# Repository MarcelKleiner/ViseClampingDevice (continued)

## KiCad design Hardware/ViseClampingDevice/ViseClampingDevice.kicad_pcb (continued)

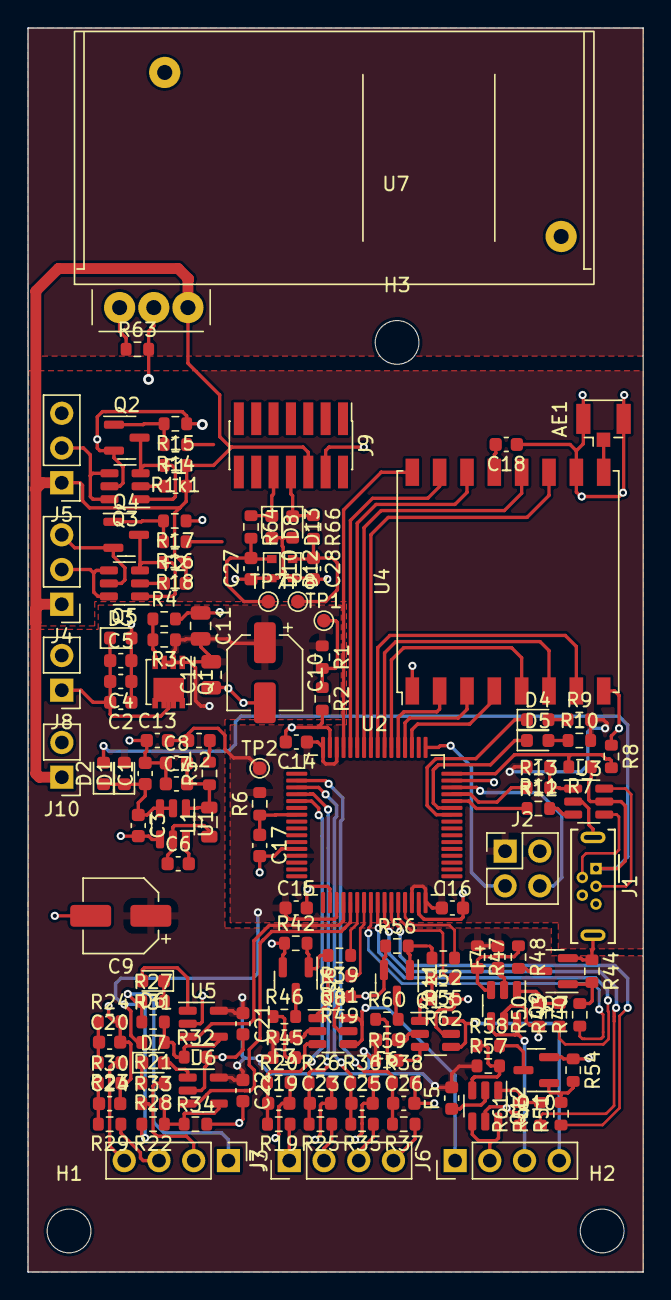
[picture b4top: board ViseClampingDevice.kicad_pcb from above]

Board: 2 copper layers, 45.0 x 91.0 mm, 151 parts (0 on the bottom side), 107 nets.

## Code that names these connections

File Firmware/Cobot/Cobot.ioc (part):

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Mcu.Name=STM32L433RCTxP
Mcu.Package=LQFP64
Mcu.UserName=STM32L433RCTxP
PA0.GPIOParameters=GPIO_Label
PA0.GPIO_Label=DI_6
PA0.Signal=GPIO_Input
PA1.GPIOParameters=GPIO_Label
PA1.GPIO_Label=DI_7
PA1.Signal=GPIO_Input
PA10.GPIOParameters=GPIO_Label
PA10.GPIO_Label=LED_G
PA10.Signal=GPIO_Output
PA11.Mode=Device
PA11.Signal=USB_DM
PA12.Mode=Device
PA12.Signal=USB_DP
PA13\ (JTMS-SWDIO).Mode=Serial_Wire
PA13\ (JTMS-SWDIO).Signal=SYS_JTMS-SWDIO
PA14\ (JTCK-SWCLK).Mode=Serial_Wire
PA14\ (JTCK-SWCLK).Signal=SYS_JTCK-SWCLK
PA2.GPIOParameters=GPIO_Label
PA2.GPIO_Label=DI_8
PA2.Signal=GPIO_Input
PA4.Signal=COMP_DAC11_group
PA5.Signal=COMP_DAC12_group
PA6.Signal=ADCx_IN11
PA7.Signal=ADCx_IN12
PA8.GPIOParameters=GPIO_Label
PA8.GPIO_Label=DI_OUT_1_P
PA8.Signal=GPIO_Output
PA9.GPIOParameters=GPIO_Label
PA9.GPIO_Label=LED_R
PA9.Signal=GPIO_Output
PB0.GPIOParameters=GPIO_Label
PB0.GPIO_Label=DI_OUT_4_P
PB0.Signal=GPIO_Output
PB1.GPIOParameters=GPIO_Label
PB1.GPIO_Label=DI_OUT_6_P
PB1.Signal=GPIO_Output
PB10.GPIOParameters=GPIO_Label
PB10.GPIO_Label=DI_OUT_4_N
PB10.Signal=GPIO_Output
PB11.GPIOParameters=GPIO_Label
PB11.GPIO_Label=DI_OUT_2_P
PB11.Signal=GPIO_Output
PB13.GPIOParameters=GPIO_Label
PB13.GPIO_Label=DI_OUT_7_N
PB13.Signal=GPIO_Output
PB14.GPIOParameters=GPIO_Label
PB14.GPIO_Label=DI_OUT_7_P
PB14.Signal=GPIO_Output
PB15.GPIOParameters=GPIO_Label
PB15.GPIO_Label=DI_OUT_5_N
PB15.Signal=GPIO_Output
PB2.GPIOParameters=GPIO_Label
PB2.GPIO_Label=DI_OUT_2_N
PB2.Signal=GPIO_Output
PB3\ (JTDO-TRACESWO).GPIOParameters=GPIO_Label
PB3\ (JTDO-TRACESWO).GPIO_Label=RFM_NSS
PB3\ (JTDO-TRACESWO).Signal=GPIO_Output
PB4\ (NJTRST).GPIOParameters=GPIO_Label
PB4\ (NJTRST).GPIO_Label=RFM_RST
PB4\ (NJTRST).Signal=GPIO_Output
PB5.GPIOParameters=GPIO_Label
PB5.GPIO_Label=RFM_DI_3
PB5.Signal=GPIO_Output
PB6.GPIOParameters=GPIO_Label
PB6.GPIO_Label=RFM_DI_0
PB6.Signal=GPIO_Output
PB7.GPIOParameters=GPIO_Label
PB7.GPIO_Label=RFM_DI_2
PB7.Signal=GPIO_Output
PC0.GPIOParameters=GPIO_Label
PC0.GPIO_Label=DI_2
PC0.Signal=GPIO_Input
PC1.GPIOParameters=GPIO_Label
PC1.GPIO_Label=DI_3
PC1.Signal=GPIO_Input
PC10.Mode=Full_Duplex_Master
PC10.Signal=SPI3_SCK
PC11.Mode=Full_Duplex_Master
PC11.Signal=SPI3_MISO
PC12.Mode=Full_Duplex_Master
PC12.Signal=SPI3_MOSI
PC14-OSC32_IN\ (PC14).GPIOParameters=GPIO_Label
PC14-OSC32_IN\ (PC14).GPIO_Label=DI_OUT_8_P
PC14-OSC32_IN\ (PC14).Signal=GPIO_Output
PC15-OSC32_OUT\ (PC15).GPIOParameters=GPIO_Label
PC15-OSC32_OUT\ (PC15).GPIO_Label=DI_OUT_8_N
PC15-OSC32_OUT\ (PC15).Signal=GPIO_Output
PC2.GPIOParameters=GPIO_Label
PC2.GPIO_Label=DI_4
PC2.Signal=GPIO_Input
PC3.GPIOParameters=GPIO_Label
PC3.GPIO_Label=DI_5
PC3.Signal=GPIO_Input
PC4.GPIOParameters=GPIO_Label
PC4.GPIO_Label=DI_OUT_6_N
PC4.Signal=GPIO_Output
PC6.GPIOParameters=GPIO_Label
PC6.GPIO_Label=DI_OUT_5_P
PC6.Signal=GPIO_Output
PC7.GPIOParameters=GPIO_Label
PC7.GPIO_Label=DI_OUT_3_N
PC7.Signal=GPIO_Output
PC8.GPIOParameters=GPIO_Label
PC8.GPIO_Label=DI_OUT_3_P
PC8.Signal=GPIO_Output
PC9.GPIOParameters=GPIO_Label
PC9.GPIO_Label=DI_OUT_1_N
PC9.Signal=GPIO_Output
PH1-OSC_OUT\ (PH1).GPIOParameters=GPIO_Label
PH1-OSC_OUT\ (PH1).GPIO_Label=DI_1
PH1-OSC_OUT\ (PH1).Signal=GPIO_Input
RCC.HSE_VALUE=8000000
RCC.SYSCLKFreq_VALUE=72000000
RCC.SYSCLKSource=RCC_SYSCLKSOURCE_PLLCLK
board=custom

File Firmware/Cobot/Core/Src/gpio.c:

/* USER CODE BEGIN Header */
/**
  ******************************************************************************
  * @file    gpio.c
  * @brief   This file provides code for the configuration
  *          of all used GPIO pins.
  ******************************************************************************
  * @attention
  *
  * Copyright (c) 2022 STMicroelectronics.
  * All rights reserved.
  *
  * This software is licensed under terms that can be found in the LICENSE file
  * in the root directory of this software component.
  * If no LICENSE file comes with this software, it is provided AS-IS.
  *
  ******************************************************************************
  */
/* USER CODE END Header */

/* Includes ------------------------------------------------------------------*/
#include "gpio.h"

/* USER CODE BEGIN 0 */

/* USER CODE END 0 */

/*----------------------------------------------------------------------------*/
/* Configure GPIO                                                             */
/*----------------------------------------------------------------------------*/
/* USER CODE BEGIN 1 */

/* USER CODE END 1 */

/** Configure pins as
        * Analog
        * Input
        * Output
        * EVENT_OUT
        * EXTI
        * Free pins are configured automatically as Analog (this feature is enabled through
        * the Code Generation settings)
*/
void MX_GPIO_Init(void)
{

  GPIO_InitTypeDef GPIO_InitStruct = {0};

  /* GPIO Ports Clock Enable */
  __HAL_RCC_GPIOC_CLK_ENABLE();
  __HAL_RCC_GPIOH_CLK_ENABLE();
  __HAL_RCC_GPIOA_CLK_ENABLE();
  __HAL_RCC_GPIOB_CLK_ENABLE();

  /*Configure GPIO pin Output Level */
  HAL_GPIO_WritePin(GPIOC, DI_OUT_8_P_Pin|DI_OUT_8_N_Pin|DI_OUT_6_N_Pin|DI_OUT_5_P_Pin
                          |DI_OUT_3_N_Pin|DI_OUT_3_P_Pin|DI_OUT_1_N_Pin, GPIO_PIN_RESET);

  /*Configure GPIO pin Output Level */
   HAL_GPIO_WritePin(GPIOB, DI_OUT_4_P_Pin|DI_OUT_6_P_Pin|DI_OUT_2_N_Pin|DI_OUT_4_N_Pin
                          |DI_OUT_2_P_Pin|DI_OUT_7_N_Pin|DI_OUT_7_P_Pin|DI_OUT_5_N_Pin
                          |RFM_NSS_Pin|RFM_RST_Pin|RFM_DI_3_Pin|RFM_DI_0_Pin
                          |RFM_DI_2_Pin, GPIO_PIN_RESET);

  /*Configure GPIO pin Output Level */
  HAL_GPIO_WritePin(GPIOA, DI_OUT_1_P_Pin|LED_R_Pin|LED_G_Pin, GPIO_PIN_RESET);

  /*Configure GPIO pin : PC13 */
  GPIO_InitStruct.Pin = GPIO_PIN_13;
  GPIO_InitStruct.Mode = GPIO_MODE_ANALOG;
  GPIO_InitStruct.Pull = GPIO_NOPULL;
  HAL_GPIO_Init(GPIOC, &GPIO_InitStruct);

  /*Configure GPIO pins : PCPin PCPin PCPin PCPin
                           PCPin PCPin PCPin */
  GPIO_InitStruct.Pin = DI_OUT_8_P_Pin|DI_OUT_8_N_Pin|DI_OUT_6_N_Pin|DI_OUT_5_P_Pin
                          |DI_OUT_3_N_Pin|DI_OUT_3_P_Pin|DI_OUT_1_N_Pin;
  GPIO_InitStruct.Mode = GPIO_MODE_OUTPUT_PP;
  GPIO_InitStruct.Pull = GPIO_NOPULL;
  GPIO_InitStruct.Speed = GPIO_SPEED_FREQ_LOW;
  HAL_GPIO_Init(GPIOC, &GPIO_InitStruct);

  /*Configure GPIO pins : PH0 PH3 */
  GPIO_InitStruct.Pin = GPIO_PIN_0|GPIO_PIN_3;
  GPIO_InitStruct.Mode = GPIO_MODE_ANALOG;
  GPIO_InitStruct.Pull = GPIO_NOPULL;
  HAL_GPIO_Init(GPIOH, &GPIO_InitStruct);

  /*Configure GPIO pin : PtPin */
  GPIO_InitStruct.Pin = DI_1_Pin;
  GPIO_InitStruct.Mode = GPIO_MODE_INPUT;
  GPIO_InitStruct.Pull = GPIO_NOPULL;
  HAL_GPIO_Init(DI_1_GPIO_Port, &GPIO_InitStruct);

  /*Configure GPIO pins : PCPin PCPin PCPin PCPin */
  GPIO_InitStruct.Pin = DI_2_Pin|DI_3_Pin|DI_4_Pin|DI_5_Pin;
  GPIO_InitStruct.Mode = GPIO_MODE_INPUT;
  GPIO_InitStruct.Pull = GPIO_NOPULL;
  HAL_GPIO_Init(GPIOC, &GPIO_InitStruct);

  /*Configure GPIO pins : PAPin PAPin PAPin */
  GPIO_InitStruct.Pin = DI_6_Pin|DI_7_Pin|DI_8_Pin;
  GPIO_InitStruct.Mode = GPIO_MODE_INPUT;
  GPIO_InitStruct.Pull = GPIO_NOPULL;
  HAL_GPIO_Init(GPIOA, &GPIO_InitStruct);

  /*Configure GPIO pins : PA3 PA15 */
  GPIO_InitStruct.Pin = GPIO_PIN_3|GPIO_PIN_15;
  GPIO_InitStruct.Mode = GPIO_MODE_ANALOG;
  GPIO_InitStruct.Pull = GPIO_NOPULL;
  HAL_GPIO_Init(GPIOA, &GPIO_InitStruct);

  /*Configure GPIO pins : PBPin PBPin PBPin PBPin
                           PBPin PBPin PBPin PBPin
                           PBPin PBPin PBPin PBPin
                           PBPin */
  GPIO_InitStruct.Pin = DI_OUT_4_P_Pin|DI_OUT_6_P_Pin|DI_OUT_2_N_Pin|DI_OUT_4_N_Pin
                          |DI_OUT_2_P_Pin|DI_OUT_7_N_Pin|DI_OUT_7_P_Pin|DI_OUT_5_N_Pin
                          |RFM_NSS_Pin|RFM_RST_Pin|RFM_DI_3_Pin|RFM_DI_0_Pin
                          |RFM_DI_2_Pin;
  GPIO_InitStruct.Mode = GPIO_MODE_OUTPUT_PP;
  GPIO_InitStruct.Pull = GPIO_NOPULL;
  GPIO_InitStruct.Speed = GPIO_SPEED_FREQ_LOW;
  HAL_GPIO_Init(GPIOB, &GPIO_InitStruct);

  /*Configure GPIO pins : PB12 PB8 PB9 */
  GPIO_InitStruct.Pin = GPIO_PIN_12|GPIO_PIN_8|GPIO_PIN_9;
  GPIO_InitStruct.Mode = GPIO_MODE_ANALOG;
  GPIO_InitStruct.Pull = GPIO_NOPULL;
  HAL_GPIO_Init(GPIOB, &GPIO_InitStruct);

  /*Configure GPIO pins : PAPin PAPin PAPin */
  GPIO_InitStruct.Pin = DI_OUT_1_P_Pin|LED_R_Pin|LED_G_Pin;
  GPIO_InitStruct.Mode = GPIO_MODE_OUTPUT_PP;
  GPIO_InitStruct.Pull = GPIO_NOPULL;
  GPIO_InitStruct.Speed = GPIO_SPEED_FREQ_LOW;
  HAL_GPIO_Init(GPIOA, &GPIO_InitStruct);

}

/* USER CODE BEGIN 2 */

/* USER CODE END 2 */

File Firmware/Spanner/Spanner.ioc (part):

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Mcu.Name=STM32L412K8Tx
Mcu.Package=LQFP32
Mcu.UserName=STM32L412K8Tx
PA0-CK_IN.GPIOParameters=GPIO_Label
PA0-CK_IN.GPIO_Label=POWER_SWITCH
PA0-CK_IN.Signal=GPIO_Output
PA1.GPIOParameters=GPIO_Label
PA1.GPIO_Label=VOLTAGE_MEASUREMENT
PA1.Signal=ADCx_IN6
PA11.Mode=Device
PA11.Signal=USB_DM
PA12.Mode=Device
PA12.Signal=USB_DP
PA13\ (JTMS/SWDIO).Mode=Serial_Wire
PA13\ (JTMS/SWDIO).Signal=SYS_JTMS-SWDIO
PA14\ (JTCK/SWCLK).Mode=Serial_Wire
PA14\ (JTCK/SWCLK).Signal=SYS_JTCK-SWCLK
PA15\ (JTDI).GPIOParameters=GPIO_Label
PA15\ (JTDI).GPIO_Label=PWM_1
PA15\ (JTDI).Signal=S_TIM2_CH1
PA2.GPIOParameters=GPIO_Label
PA2.GPIO_Label=CURRENT_MEASUREMENT
PA2.Signal=ADCx_IN7
PA3.GPIOParameters=GPIO_Label
PA3.GPIO_Label=RFM_RST
PA3.Signal=GPIO_Output
PA4.GPIOParameters=GPIO_Label
PA4.GPIO_Label=RFM_NSS
PA4.Signal=GPIO_Output
PA5.Mode=Full_Duplex_Master
PA5.Signal=SPI1_SCK
PA6.Mode=Full_Duplex_Master
PA6.Signal=SPI1_MISO
PA7.Mode=Full_Duplex_Master
PA7.Signal=SPI1_MOSI
PA8.Signal=S_TIM1_CH1
PA9.Signal=S_TIM1_CH2
PB0.GPIOParameters=GPIO_Label
PB0.GPIO_Label=RFM_DI2
PB0.Signal=GPIO_Input
PB1.GPIOParameters=GPIO_Label
PB1.GPIO_Label=VUSB
PB1.Signal=GPIO_Input
PB3\ (JTDO/TRACESWO).GPIOParameters=GPIO_Label
PB3\ (JTDO/TRACESWO).GPIO_Label=PWM_2
PB3\ (JTDO/TRACESWO).Signal=S_TIM2_CH2
PB4\ (NJTRST).GPIOParameters=GPIO_Label
PB4\ (NJTRST).GPIO_Label=LED_EXT
PB4\ (NJTRST).Signal=GPIO_Output
PB5.GPIOParameters=GPIO_Label
PB5.GPIO_Label=SW_EXT
PB5.Signal=GPIO_Input
PB7.GPIOParameters=GPIO_Label
PB7.GPIO_Label=LED
PB7.Signal=GPIO_Output
PC14-OSC32_IN\ (PC14).GPIOParameters=GPIO_Label
PC14-OSC32_IN\ (PC14).GPIO_Label=RFM_DI0
PC14-OSC32_IN\ (PC14).Signal=GPIO_Input
PC15-OSC32_OUT\ (PC15).GPIOParameters=GPIO_Label
PC15-OSC32_OUT\ (PC15).GPIO_Label=RFM_DI3
PC15-OSC32_OUT\ (PC15).Signal=GPIO_Input
RCC.HSE_VALUE=8000000
RCC.SYSCLKFreq_VALUE=64000000
RCC.SYSCLKSource=RCC_SYSCLKSOURCE_PLLCLK
board=custom

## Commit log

2022-10-18 HW design spanner and cobot
2022-10-24 softwareproject added
2022-11-13 Software implementation
2022-11-27 update software
2022-12-10 Update Firmware
2022-12-10 USB Update
2022-12-11 update gui
2022-12-17 update GUI and USB CDC
2022-12-18 update USB
2022-12-26 Update various modules
2022-12-27 update spanner
2022-12-27 update drive
2023-01-22 FW update
2023-07-03 Update HW and SW
2023-11-25 stabilize cobot software
2023-11-26 software stabilisation
2023-11-30 add new config software
2023-11-30 no message
2023-12-19 updat Teach mode and configuration tool
